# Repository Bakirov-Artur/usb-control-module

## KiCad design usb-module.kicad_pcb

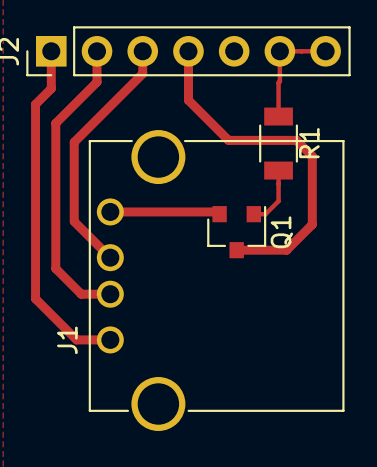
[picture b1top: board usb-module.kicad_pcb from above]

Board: 2 copper layers, 4 parts (0 on the bottom side), 8 nets.

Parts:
J1: USB_A
J2: CONN_01X07; Pin_Header_Straight_1x07_Pitch2.54mm
Q1: irlml6344; SOT-23
R1: R; C_1206

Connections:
GND: J1.5, J2.5
unnamed: J1.1, J2.1
unnamed: J1.2, J2.2
unnamed: J1.3, J2.3
unnamed: J1.4, Q1.2
unnamed: J2.4, Q1.3
unnamed: J2.6, J2.7, R1.1
unnamed: Q1.1, R1.2

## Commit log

2017-07-23 initial
